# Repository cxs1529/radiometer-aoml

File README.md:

# newrepo
newrepo

MESSAGE FROM THE HUB

HELLOOOOOO FROM THE HUB

FROM THE HUB

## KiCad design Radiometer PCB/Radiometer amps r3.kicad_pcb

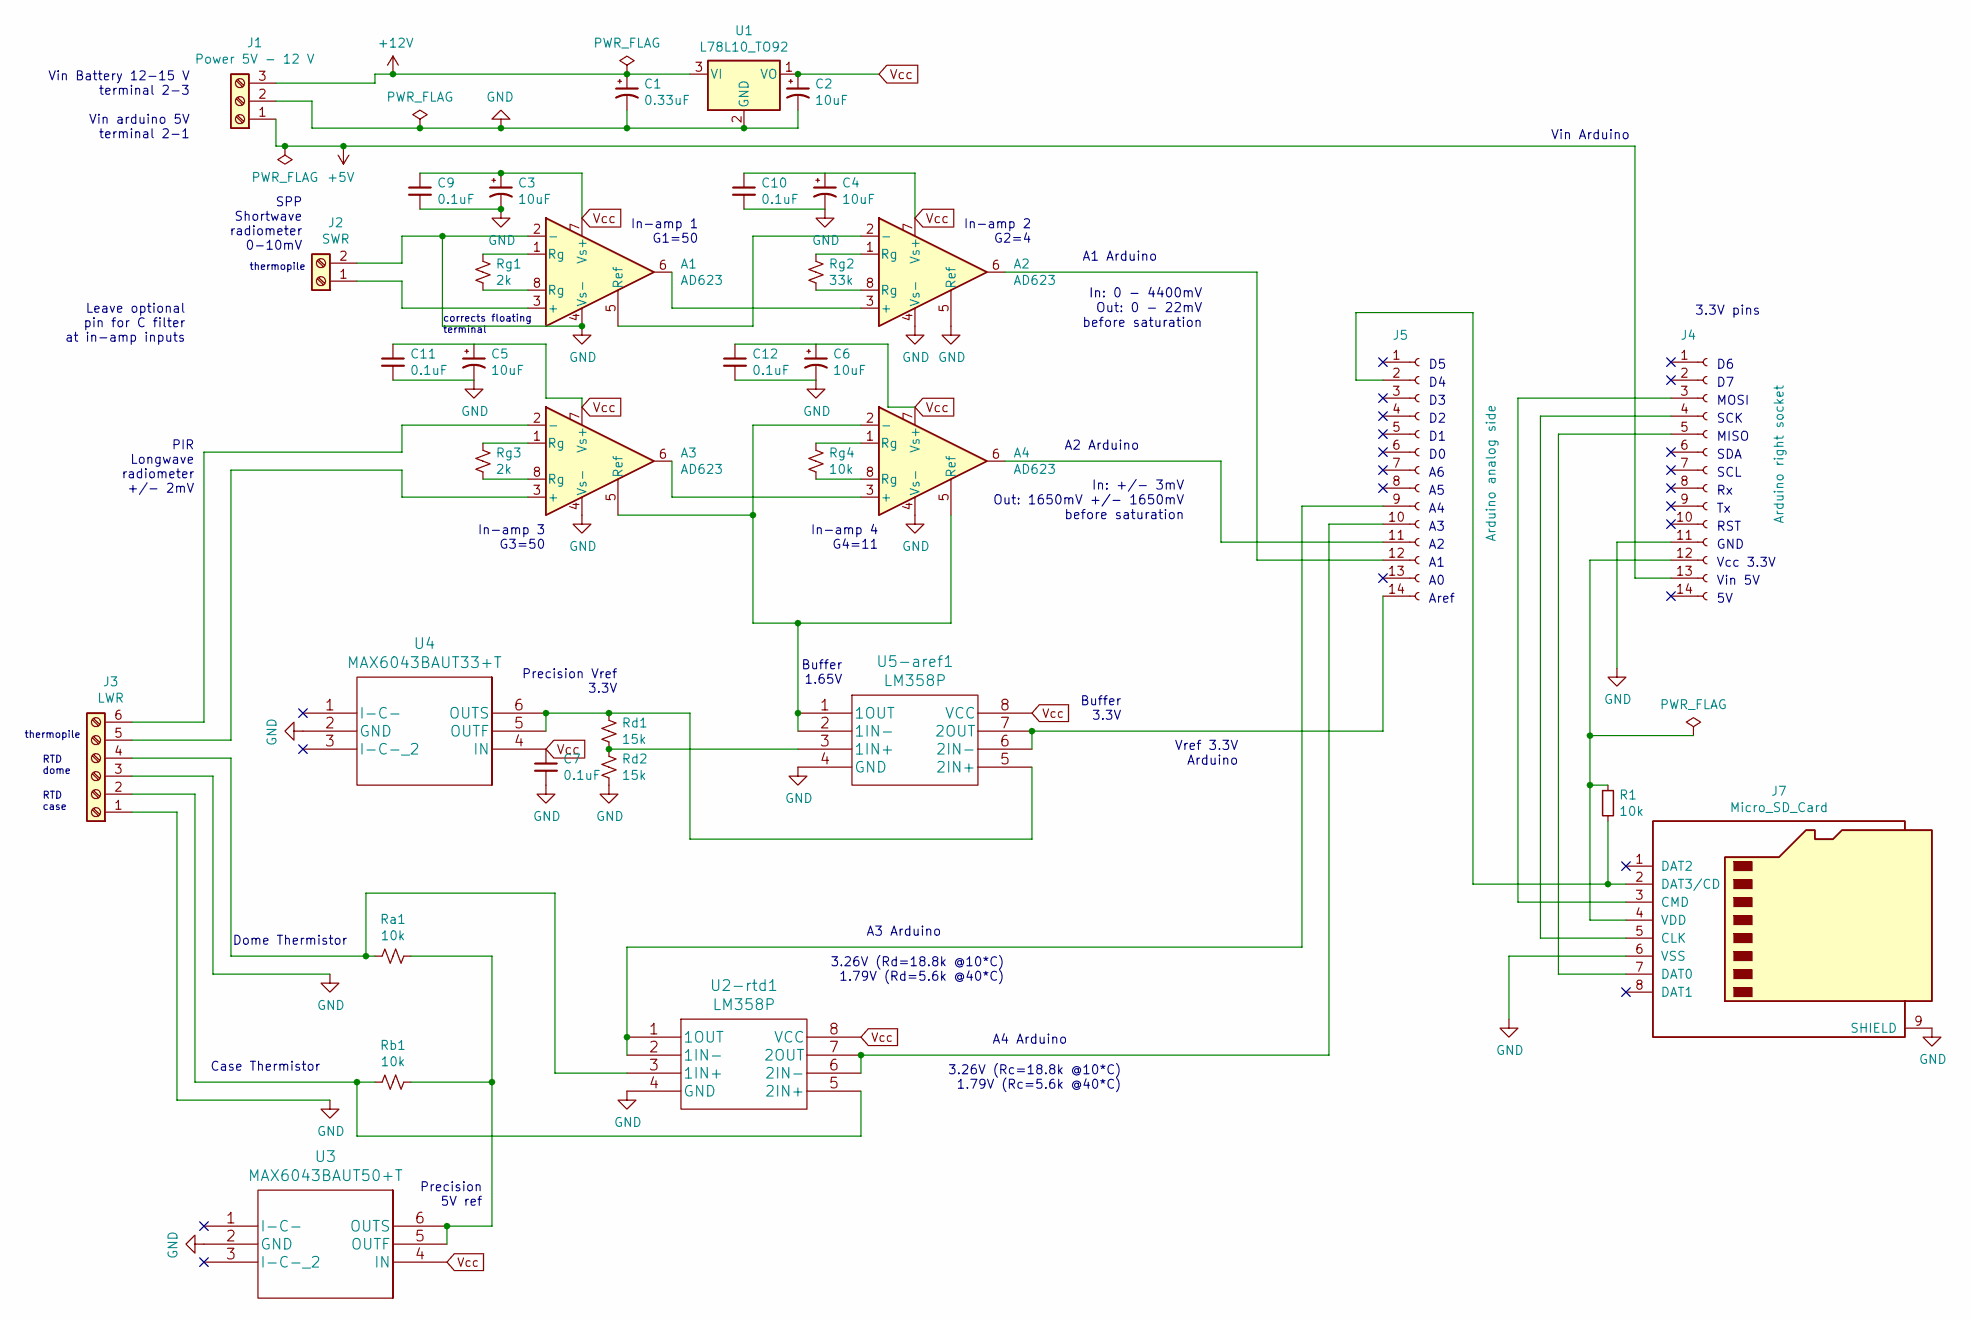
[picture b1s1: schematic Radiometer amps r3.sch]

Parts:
A1, A2, A3, A4: AD623; DIP-8_W7.62mm
C1: 0.33uF; CP_Radial_D5.0mm_P2.00mm
C2, C3, C4, C5, C6: 10uF; CP_Radial_D5.0mm_P2.00mm
C7, C9, C10, C11, C12: 0.1uF; C_Rect_L7.0mm_W2.5mm_P5.00mm
J1: Power 5V - 12 V; Term_Block_1x3_P5mm
J2: SWR; Term_Block_1x2_P5mm
J3: LWR; Term_Block_1x6_P5mm
J4: Arduino right socket; PinSocket_1x14_P2.54mm_Vertical
J5: Arduino analog side; PinSocket_1x14_P2.54mm_Vertical
J7: Micro_SD_Card; microSD_HC_Wuerth_693072010801
R1: 10k; R_Axial_DIN0207_L6.3mm_D2.5mm_P10.16mm_Horizontal
Ra1: 10k; R_Axial_DIN0207_L6.3mm_D2.5mm_P10.16mm_Horizontal
Rb1: 10k; R_Axial_DIN0207_L6.3mm_D2.5mm_P10.16mm_Horizontal
Rd1, Rd2: 15k; R_Axial_DIN0207_L6.3mm_D2.5mm_P10.16mm_Horizontal
Rg1, Rg3: 2k; R_Axial_DIN0207_L6.3mm_D2.5mm_P10.16mm_Horizontal
Rg2: 33k; R_Axial_DIN0207_L6.3mm_D2.5mm_P10.16mm_Horizontal
Rg4: 10k; R_Axial_DIN0207_L6.3mm_D2.5mm_P10.16mm_Horizontal
U1: L78L10_TO92; TO-92_Inline
U2-rtd1, U5-aref1: LM358P; DIP-8_W7.62mm
U3: MAX6043BAUT50+T; MAX6043AAUT33-G16
U4: MAX6043BAUT33+T; MAX6043AAUT33-G16

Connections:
+5V: J1.1, J4.13
+12V: C1.1, J1.3, U1.3 (VI)
GND: A1.2 (-), A1.4 (Vs-), A2.4 (Vs-), A2.5 (Ref), A3.4 (Vs-), A4.4 (Vs-), C1.2, C2.2, C3.2, C4.2, C5.2, C6.2, C7.2, C9.2, C10.2, C11.2, C12.2, J1.2, J2.2, J3.1, J3.3, J4.11, J7.6 (VSS), J7.9 (SHIELD), Rd2.2, U1.2 (GND), U2-rtd1.4 (GND), U3.2 (GND), U4.2 (GND), U5-aref1.4 (GND)
unnamed: A1.1 (Rg), Rg1.1
unnamed: A1.3 (+), J2.1
unnamed: A1.5 (Ref), A2.2 (-)
unnamed: A1.6, A2.3 (+)
unnamed: A1.8 (Rg), Rg1.2
unnamed: A2.1 (Rg), Rg2.1
unnamed: A2.6, J5.12
unnamed: A2.8 (Rg), Rg2.2
unnamed: A3.1 (Rg), Rg3.1
unnamed: A3.2 (-), J3.6
unnamed: A3.3 (+), J3.5
unnamed: A3.5 (Ref), A4.2 (-), A4.5 (Ref), U5-aref1.1 (1OUT), U5-aref1.2 (1IN-)
unnamed: A3.6, A4.3 (+)
unnamed: A3.8 (Rg), Rg3.2
unnamed: A4.1 (Rg), Rg4.1
unnamed: A4.6, J5.11
unnamed: A4.8 (Rg), Rg4.2
unnamed: J3.2, Rb1.1, U2-rtd1.5 (2IN+)
unnamed: J3.4, Ra1.1, U2-rtd1.3 (1IN+)
unnamed: J4.3, J7.3 (CMD)
unnamed: J4.4, J7.5 (CLK)
unnamed: J4.5, J7.7 (DAT0)
unnamed: J4.12, J7.4 (VDD), R1.1
unnamed: J5.2, J7.2 (DAT3/CD), R1.2
unnamed: J5.9, U2-rtd1.1 (1OUT), U2-rtd1.2 (1IN-)
unnamed: J5.10, U2-rtd1.6 (2IN-), U2-rtd1.7 (2OUT)
unnamed: J5.14, U5-aref1.6 (2IN-), U5-aref1.7 (2OUT)
unnamed: Ra1.2, Rb1.2, U3.5 (OUTF), U3.6 (OUTS)
unnamed: Rd1.1, U4.5 (OUTF), U4.6 (OUTS), U5-aref1.5 (2IN+)
unnamed: Rd1.2, Rd2.1, U5-aref1.3 (1IN+)
Vcc: A1.7 (Vs+), A2.7 (Vs+), A3.7 (Vs+), A4.7 (Vs+), C2.1, C3.1, C4.1, C5.1, C6.1, C7.1, C9.1, C10.1, C11.1, C12.1, U1.1 (VO), U2-rtd1.8 (VCC), U3.4 (IN), U4.4 (IN), U5-aref1.8 (VCC)

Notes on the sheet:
A2 Arduino
A1 Arduino
Buffer 3.3V
Buffer 1.65V
Precision Vref 3.3V
Vref 3.3V Arduino
In-amp 4 G4=11
In-amp 3 G3=50
PIR Longwave radiometer +/- 2mV
In-amp 2 G2=4
In-amp 1 G1=50
SPP Shortwave radiometer 0-10mV
A3 Arduino
A4 Arduino
In: 0 - 4400mV Out: 0 - 22mV before saturation
In: +/- 3mV Out: 1650mV +/- 1650mV before saturation
Case Thermistor
Dome Thermistor
3.26V (Rc=18.8k @10*C) 1.79V (Rc=5.6k @40*C)
3.26V (Rd=18.8k @10*C) 1.79V (Rd=5.6k @40*C)
Vin Arduino
Leave optional pin for C filter at in-amp inputs
thermopile
RTD case
RTD dome
Aref
Vin 5V
Vcc 3.3V
GND
Precision 5V ref
RST
SCL
SDA
MISO
SCK
MOSI
3.3V pins
Vin Battery 12-15 V terminal 2-3 Vin arduino 5V terminal 2-1
corrects floating terminal

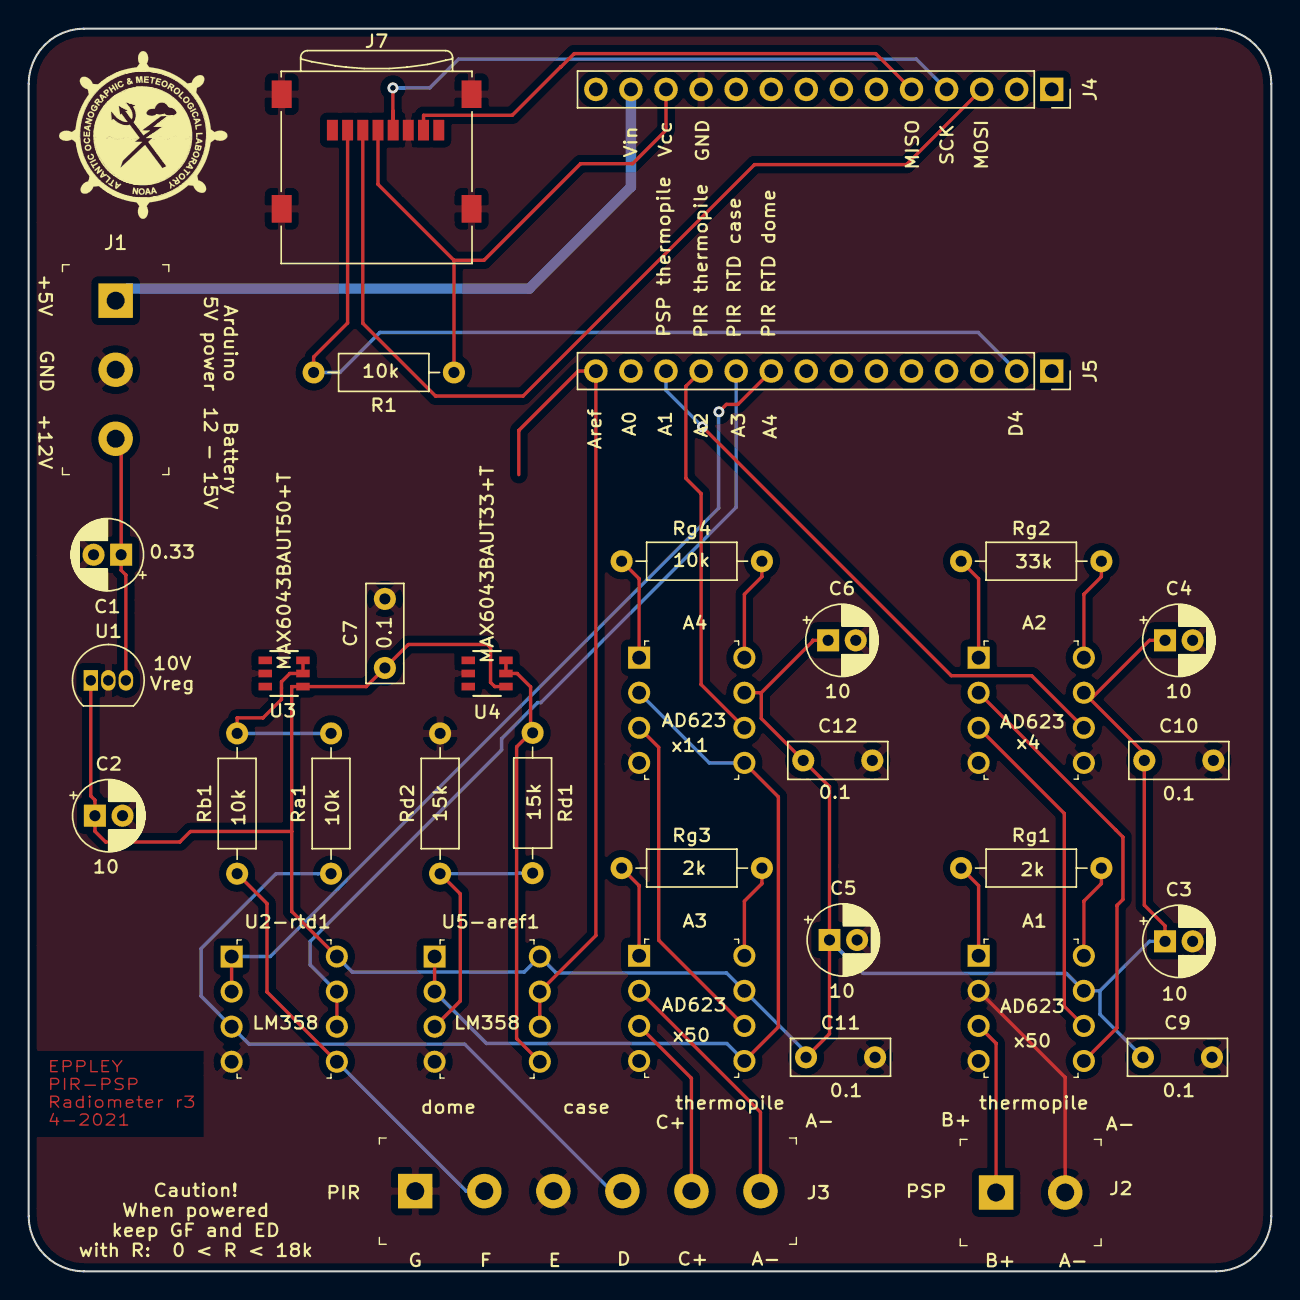
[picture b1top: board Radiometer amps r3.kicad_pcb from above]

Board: 2 copper layers, 90.0 x 90.0 mm, 35 parts (0 on the bottom side), 34 nets.

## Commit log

2020-03-30 Upload of version 3 prototype variants
    rtc_and_sd_working - refers to the last stable/deployed version of firmware for the radiometer system
    RTCSD_Gain - refers to an update made for gain non-linearity compensation
    rtc_and_sd_working_REVA - refers to a restructured version of "rtc_and_sd_working" based on OOD
2020-03-31 commit test for a simple text file
2020-03-31 second commit
2020-03-31 boo commit
2020-03-31 hmmm...
2020-03-31 poop test commit
2020-03-31 testing LOL commit to dumb branch
2020-03-31 message update in anothertest
2020-04-01 pushing derp.txt to local master
2020-04-01 new directory, new rules
2020-04-02 RTCSD gain condition error fixed
2020-04-14 Add files via upload
    This code is based on the MKRGSM FTP library: https://github.com/tryhus/MKRGSM/tree/feature/ftp
    An Arduino MKR GSM 1400 with a SIM card with internet is needed for this project.
    The program reads 2 analog values and with a time stamp creates a string with a fixed format MMDDYYhhmmssAAAABBBB every second (this can be changed in line 239).
    The string may be "compressed" to reduce data traffic, changing the number's base, from decimal to other base like hexadecimal or base 36 (using 0-9...A-Z). The latter will reduce the Max number of 1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
2020-04-14 FTP upload
    This code is based on the MKRGSM FTP library: https://github.com/tryhus/MKRGSM/tree/feature/ftp
    An Arduino MKR GSM 1400 with a SIM card with internet is needed for this project.
    The program reads 2 analog values and with a time stamp creates a string with a fixed format MMDDYYhhmmssAAAABBBB every second (this can be changed in line 239).
    The string may be "compressed" to reduce data traffic, changing the number's base, from decimal to other base like hexadecimal or base 36 (using 0-9...A-Z). The latter will reduce the Max number of 1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
2024-10-14 KiCAD files uploaded
2024-10-14 Rename Readme to Readme
2024-10-14 Rename Data_logger_Radiometer_v3_rtc_and_sd_working.ino to Radiometer firmware/Data_logger_Radiometer_v3_rtc_and_sd_working.ino

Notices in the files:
parts and their libraries:
Copyright 2016 Accelerated Designs. All rights reserved.
